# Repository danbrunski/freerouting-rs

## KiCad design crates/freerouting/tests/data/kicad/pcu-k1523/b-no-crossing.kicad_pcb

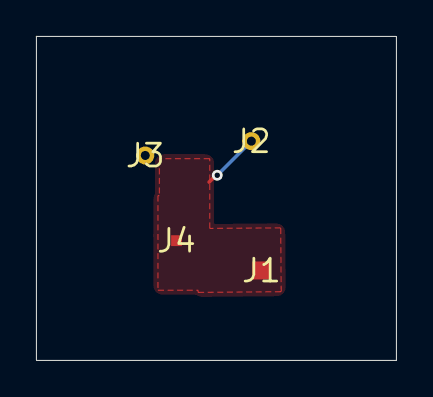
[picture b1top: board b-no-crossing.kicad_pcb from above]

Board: 4 copper layers, 20.0 x 18.0 mm, 4 parts (0 on the bottom side), 2 nets.

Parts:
J1, J4: x; smd
J2, J3: x; tht

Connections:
/CH6_NO: J1.1, J2.1
unnamed: J3.1, J4.1
